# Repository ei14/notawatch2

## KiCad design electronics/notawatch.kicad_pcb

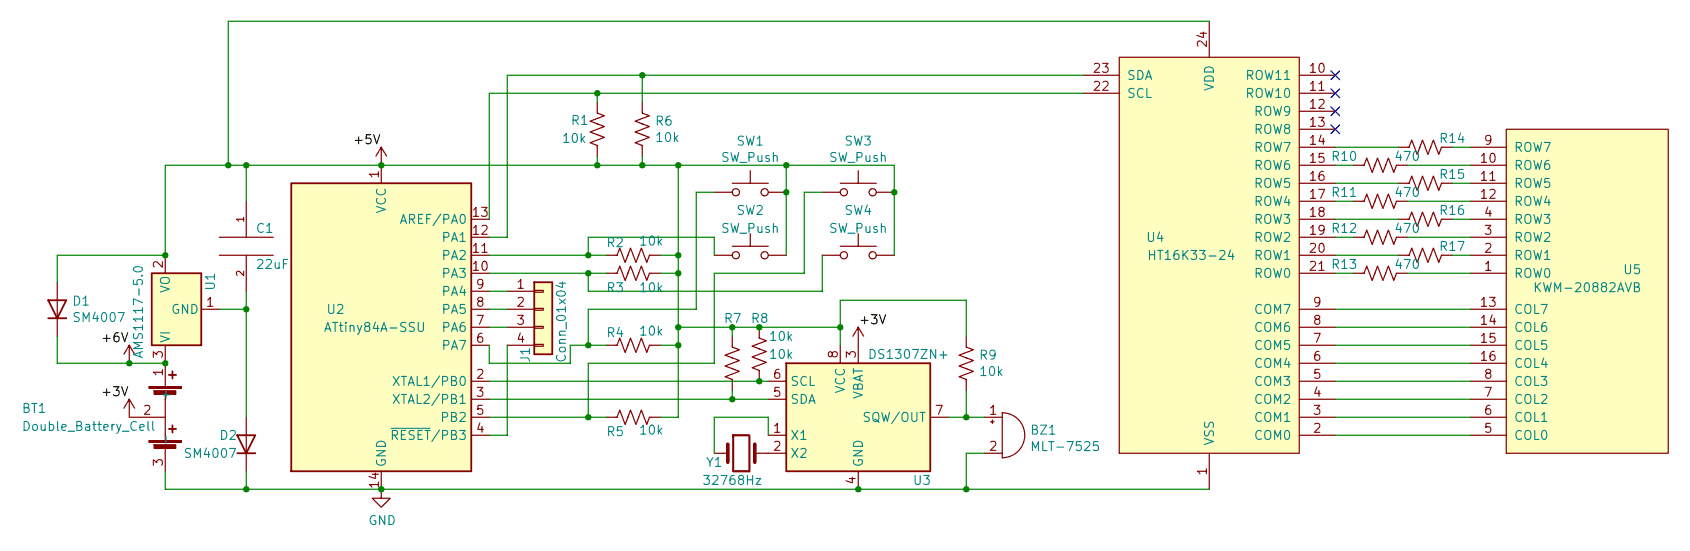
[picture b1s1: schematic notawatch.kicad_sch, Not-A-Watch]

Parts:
BT1: Double_Battery_Cell; PinHeader_1x03_P2.54mm_Vertical
BZ1: MLT-7525
C1: 22uF; C_1206_3216Metric
D1, D2: SM4007; D_MELF
J1: Conn_01x04; PinHeader_1x04_P2.54mm_Vertical
R1, R2, R3, R4, R5, R6, R7, R8, R9: 10k; R_0603_1608Metric
R10, R11, R12, R13, R14, R15, R16, R17: 470; R_0603_1608Metric
SW1, SW2, SW3, SW4: SW_Push; SW_PUSH_6mm
U1: AMS1117-5.0; SOT-223-3_TabPin2
U2: ATtiny84A-SSU; SOIC-14_3.9x8.7mm_P1.27mm
U3: DS1307ZN+; SOIC-8_3.9x4.9mm_P1.27mm
U4: HT16K33-24; SOIC-24W_7.5x15.4mm_P1.27mm
U5: KWM-20882AVB; KVM-20882AVB
Y1: 32768Hz; Crystal_Round_D2.0mm_Vertical

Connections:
+3V3: BT1.2, U3.3 (VBAT)
+5V: C1.1, D1.2 (A), R1.2, R2.1, R3.1, R4.1, R5.1, R6.2, R7.1, R8.1, R9.1, SW1.2, SW2.2, SW3.2, SW4.2, U1.2 (VO), U2.1 (VCC), U3.8 (VCC), U4.24 (VDD)
+BATT: BT1.1 (+), D1.1 (K), U1.3 (VI)
GND: BT1.3 (-), BZ1.2 (+), D2.1 (K), U2.14 (GND), U3.4 (GND), U4.1 (VSS)
unnamed: BZ1.1 (-), R9.2, U3.7 (SQW/OUT)
unnamed: C1.2, D2.2 (A), U1.1 (GND)
unnamed: J1.1, U2.9 (PA4)
unnamed: J1.2, U2.8 (PA5)
unnamed: J1.3, U2.7 (PA6)
unnamed: J1.4, U2.4 (~RESET/PB3)
unnamed: R1.1, U2.13 (AREF/PA0), U4.22 (SCL)
unnamed: R2.2, SW2.1, U2.11 (PA2)
unnamed: R3.2, SW4.1, U2.10 (PA3)
unnamed: R4.2, SW1.1, U2.6 (PA7)
unnamed: R5.2, SW3.1, U2.5 (PB2)
unnamed: R6.1, U2.12 (PA1), U4.23 (SDA)
unnamed: R7.2, U2.3 (XTAL2/PB1), U3.5 (SDA)
unnamed: R8.2, U2.2 (XTAL1/PB0), U3.6 (SCL)
unnamed: R10.1, U5.10 (ROW6)
unnamed: R10.2, U4.15 (ROW6)
unnamed: R11.1, U5.12 (ROW4)
unnamed: R11.2, U4.17 (ROW4)
unnamed: R12.1, U5.3 (ROW2)
unnamed: R12.2, U4.19 (ROW2)
unnamed: R13.1, U5.1 (ROW0)
unnamed: R13.2, U4.21 (ROW0)
unnamed: R14.1, U5.9 (ROW7)
unnamed: R14.2, U4.14 (ROW7)
unnamed: R15.1, U5.11 (ROW5)
unnamed: R15.2, U4.16 (ROW5)
unnamed: R16.1, U5.4 (ROW3)
unnamed: R16.2, U4.18 (ROW3)
unnamed: R17.1, U5.2 (ROW1)
unnamed: R17.2, U4.20 (ROW1)
unnamed: U3.1 (X1), Y1.1
unnamed: U3.2 (X2), Y1.2
unnamed: U4.2 (COM0), U5.5 (COL0)
unnamed: U4.3 (COM1), U5.6 (COL1)
unnamed: U4.4 (COM2), U5.7 (COL2)
unnamed: U4.5 (COM3), U5.8 (COL3)
unnamed: U4.6 (COM4), U5.16 (COL4)
unnamed: U4.7 (COM5), U5.15 (COL5)
unnamed: U4.8 (COM6), U5.14 (COL6)
unnamed: U4.9 (COM7), U5.13 (COL7)

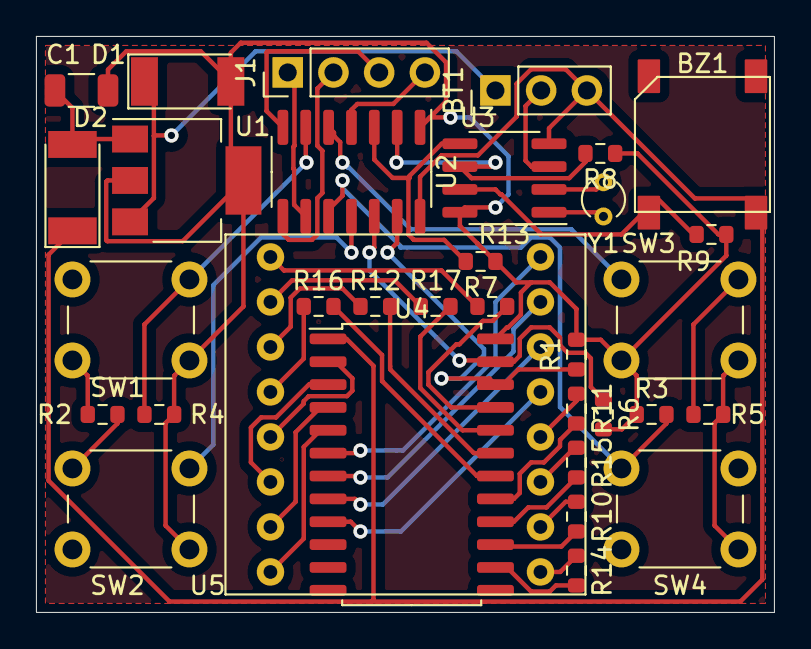
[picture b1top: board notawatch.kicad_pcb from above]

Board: 2 copper layers, 41.0 x 32.0 mm, 33 parts (0 on the bottom side), 44 nets.

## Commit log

2021-12-24 Wrote code
2021-12-25 Added time mode and sleep mode
2021-12-31 Trust me, I'm usually more dilligent about documenting git changes
